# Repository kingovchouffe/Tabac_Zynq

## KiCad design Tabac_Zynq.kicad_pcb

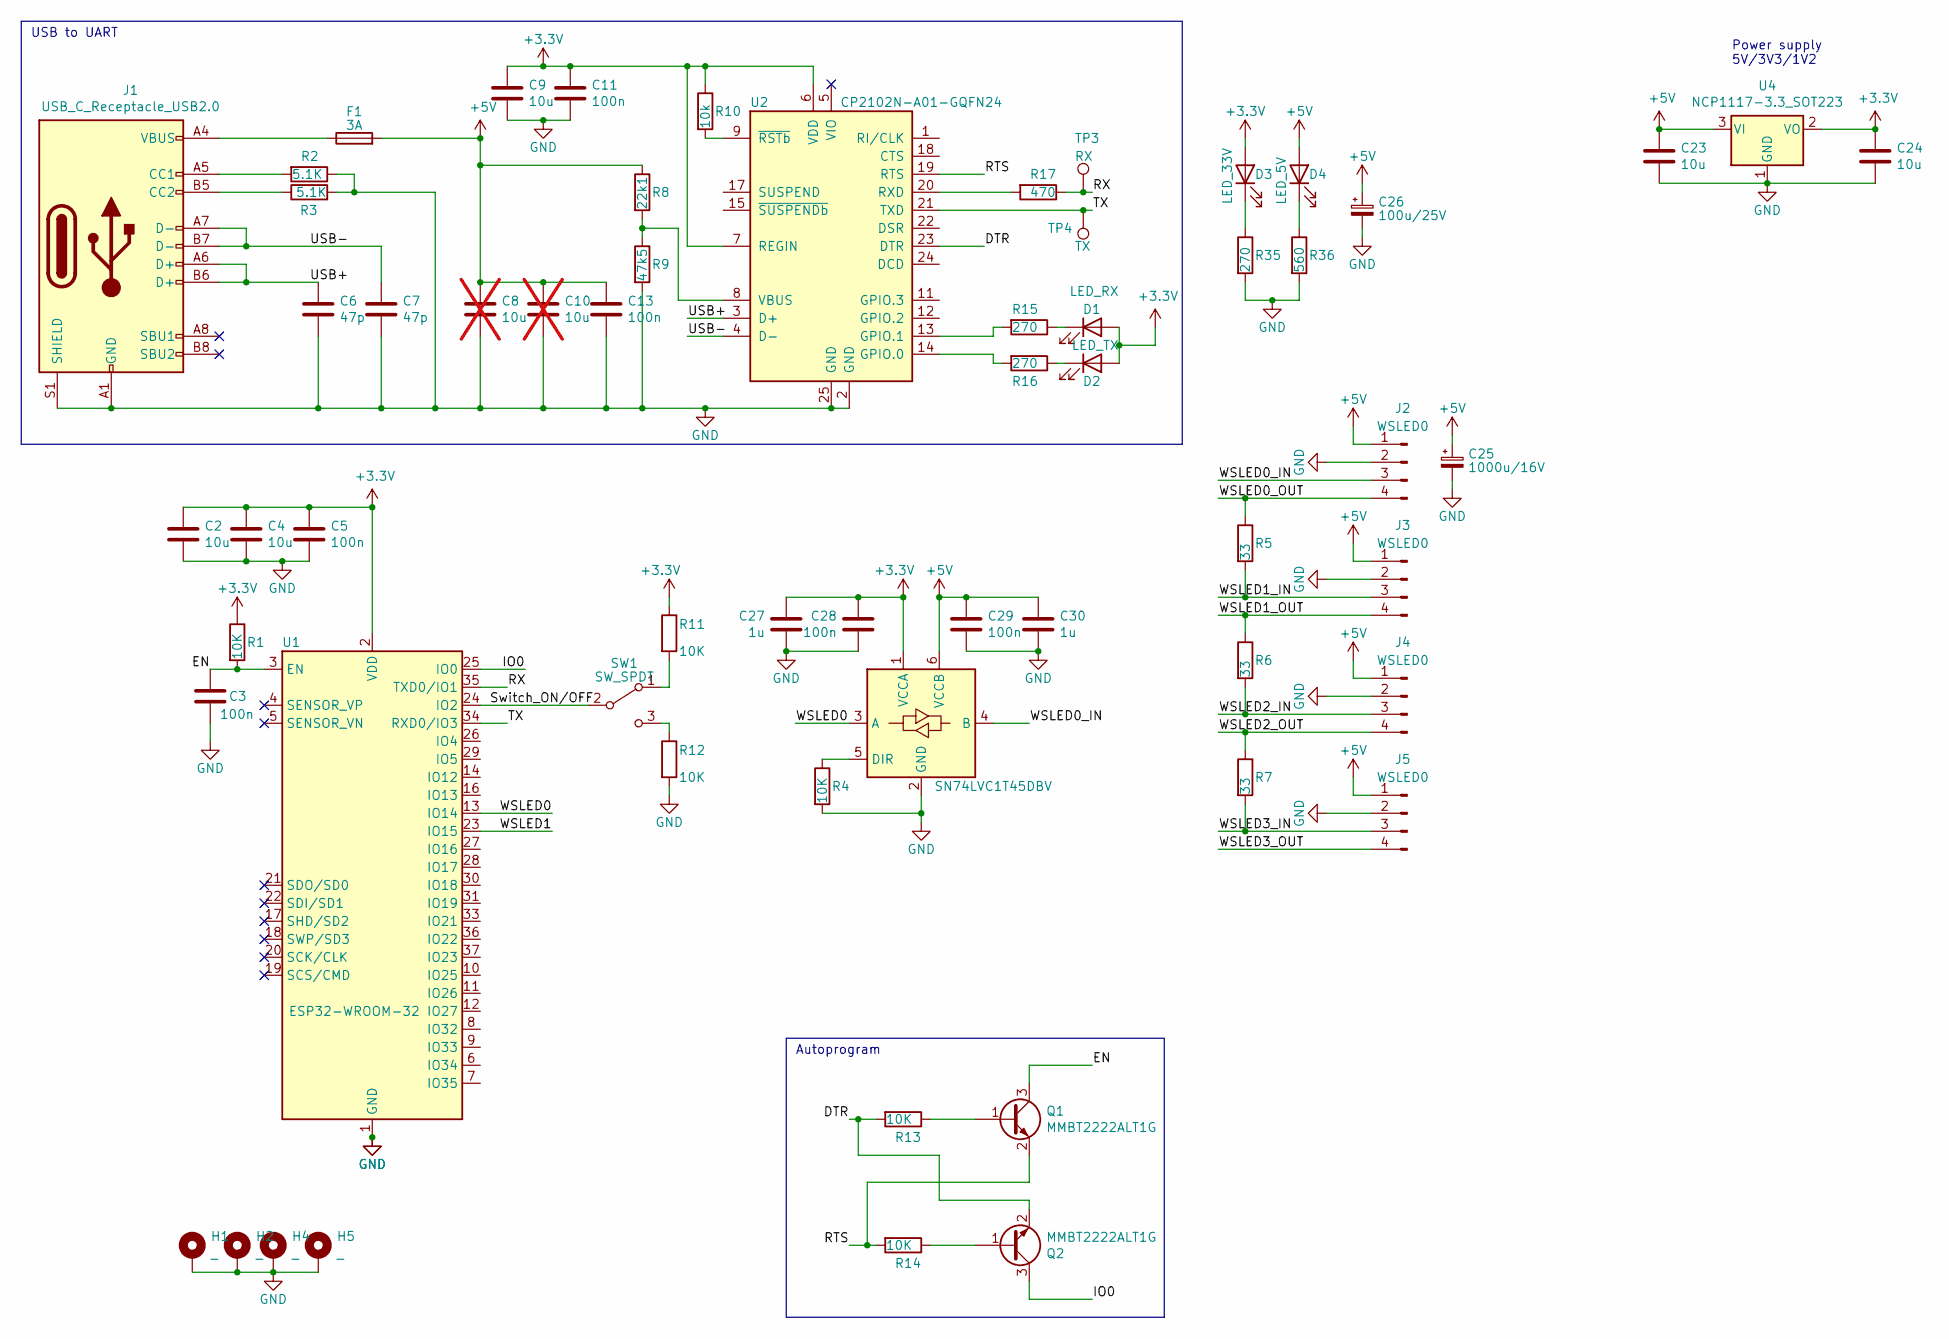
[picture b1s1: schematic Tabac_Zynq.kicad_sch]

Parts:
C2, C4, C9, C23, C24: 10u; C_0805_2012Metric
C3, C5, C11, C13, C28, C29: 100n; C_0805_2012Metric
C6, C7: 47p; C_0805_2012Metric
C8, C10: 10u; C_0805_2012Metric; not fitted
C25: 1000u/16V; CP_Elec_10x10.5
C26: 100u/25V; CP_Elec_6.3x7.7
C27, C30: 1u; C_0805_2012Metric
D1: LED_RX; LED_0805_2012Metric
D2: LED_TX; LED_0805_2012Metric
D3: LED_33V; LED_0805_2012Metric
D4: LED_5V; LED_0805_2012Metric
F1: 3A; FUSE_3557-2
H1, H2, H4, H5: _; MountingHole_3.2mm_M3_Pad_Via
J1: USB_C_Receptacle_USB2.0; USB_C_Receptacle_GCT_USB4085
J2, J3, J4, J5: WSLED0; PinSocket_1x04_P2.54mm_Vertical
Q1, Q2: MMBT2222ALT1G; SOT-23
R1, R4, R11, R12, R13, R14: 10K; R_0805_2012Metric
R2, R3: 5.1K; R_0805_2012Metric
R5, R6, R7: 33; R_0805_2012Metric
R8: 22k1; R_0805_2012Metric
R9: 47k5; R_0805_2012Metric
R10: 10k; R_0805_2012Metric
R15, R16, R35: 270; R_0805_2012Metric
R17: 470; R_0805_2012Metric
R36: 560; R_0805_2012Metric
SW1: SW_SPDT; JST_PH_B3B-PH-K_1x03_P2.00mm_Vertical
TP3: RX; TestPoint_Pad_D1.0mm
TP4: TX; TestPoint_Pad_D1.0mm
U1: ESP32-WROOM-32
U2: CP2102N-A01-GQFN24; QFN-24-1EP_4x4mm_P0.5mm_EP2.6x2.6mm
U3: SN74LVC1T45DBV; SOT-23-6
U4: NCP1117-3.3_SOT223; SOT-223-3_TabPin2

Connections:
+3V3: C2.1, C4.1, C5.1, C9.1, C11.1, C24.1, C27.1, C28.1, D1.2 (A), D2.2 (A), D3.2 (A), R1.1, R10.1, R11.1, U1.2 (VDD), U2.6 (VDD), U2.7 (REGIN), U3.1 (VCCA), U4.2 (VO)
+5V: C8.1, C10.1, C13.1, C23.1, C25.1, C26.1, C29.1, C30.1, D4.2 (A), F1.2, J2.1, J3.1, J4.1, J5.1, R8.1, U3.6 (VCCB), U4.3 (VI)
/DTR: Q2.2 (E), R13.2, U2.23 (DTR)
/EN: C3.2, Q1.3 (C), R1.2, U1.3 (EN)
/IO0: Q2.3 (C), U1.25 (IO0)
/RTS: Q1.2 (E), R14.2, U2.19 (RTS)
/RX: R17.1, TP3.1, U1.35 (TXD0/IO1)
/Switch_ON/OFF: SW1.2 (B), U1.24 (IO2)
/TX: TP4.1, U1.34 (RXD0/IO3), U2.21 (TXD)
/USB+: C6.1, J1.A6 (D+), J1.B6 (D+), U2.3 (D+)
/USB-: C7.1, J1.A7 (D-), J1.B7 (D-), U2.4 (D-)
/WSLED0: U1.13 (IO14), U3.3 (A)
/WSLED0_IN: J2.3, U3.4 (B)
/WSLED0_OUT: J2.4, R5.1
/WSLED1: U1.23 (IO15)
/WSLED1_IN: J3.3, R5.2
/WSLED1_OUT: J3.4, R6.1
/WSLED2_IN: J4.3, R6.2
/WSLED2_OUT: J4.4, R7.1
/WSLED3_IN: J5.3, R7.2
/WSLED3_OUT: J5.4
GND: C2.2, C3.1, C4.2, C5.2, C6.2, C7.2, C8.2, C9.2, C10.2, C11.2, C13.2, C23.2, C24.2, C25.2, C26.2, C27.2, C28.2, C29.2, C30.2, H1.1, H2.1, H4.1, H5.1, J1.A1 (GND), J1.A12 (GND), J1.B1 (GND), J1.B12 (GND), J1.S1 (SHIELD), J2.2, J3.2, J4.2, J5.2, R2.1, R3.2, R4.2, R9.2, R12.2, R35.2, R36.2, U1.1 (GND), U1.15 (GND), U1.38 (GND), U1.39 (GND), U2.2 (GND), U2.25 (GND), U3.2 (GND), U4.1 (GND)
unnamed: D1.1 (K), R15.1
unnamed: D2.1 (K), R16.1
unnamed: D3.1 (K), R35.1
unnamed: D4.1 (K), R36.1
unnamed: F1.1, J1.A4 (VBUS), J1.A9 (VBUS), J1.B4 (VBUS), J1.B9 (VBUS)
unnamed: J1.A5 (CC1), R2.2
unnamed: J1.B5 (CC2), R3.1
unnamed: Q1.1 (B), R13.1
unnamed: Q2.1 (B), R14.1
unnamed: R11.2, SW1.1 (A)
unnamed: R12.1, SW1.3 (C)
unnamed: R16.2, U2.14 (GPIO.0)
unnamed: R15.2, U2.13 (GPIO.1)
unnamed: R17.2, U2.20 (RXD)
unnamed: R8.2, R9.1, U2.8 (VBUS)
unnamed: R10.2, U2.9 (~RSTb)
unnamed: R4.1, U3.5 (DIR)

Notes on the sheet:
USB to UART
Autoprogram
Power supply 5V/3V3/1V2

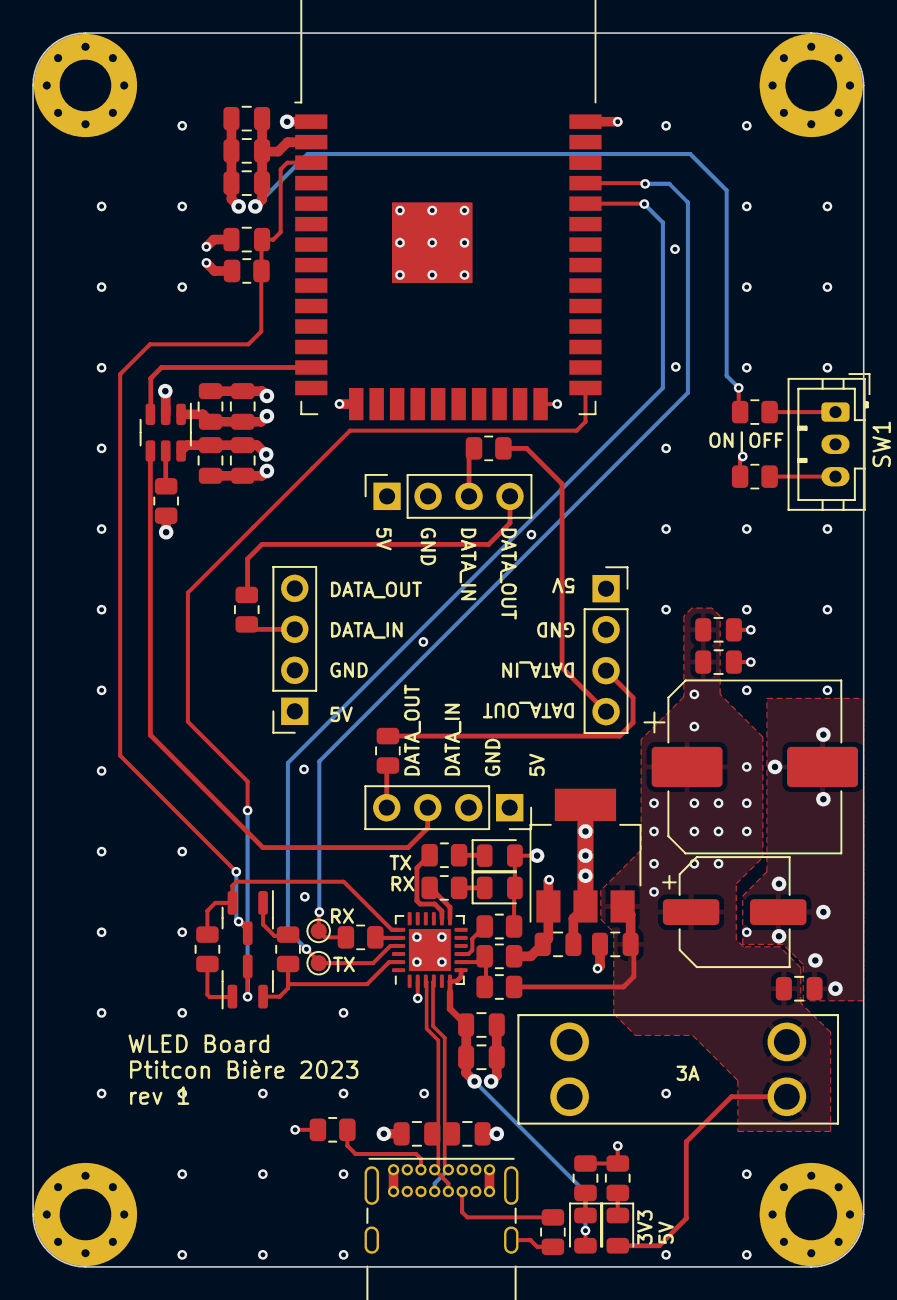
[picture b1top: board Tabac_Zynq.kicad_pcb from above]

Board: 4 copper layers, 51.5 x 76.5 mm, 61 parts (0 on the bottom side), 37 nets.

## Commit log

2023-02-27 schematic finished
2023-03-03 Start routing
2023-05-08 last update
